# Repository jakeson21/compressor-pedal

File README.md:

# compressor-pedal
This schematic implements [this compressor simulation](https://github.com/jakeson21/circuitjs_designs/blob/main/Compressor-20230116-2301.circuitjs.txt).

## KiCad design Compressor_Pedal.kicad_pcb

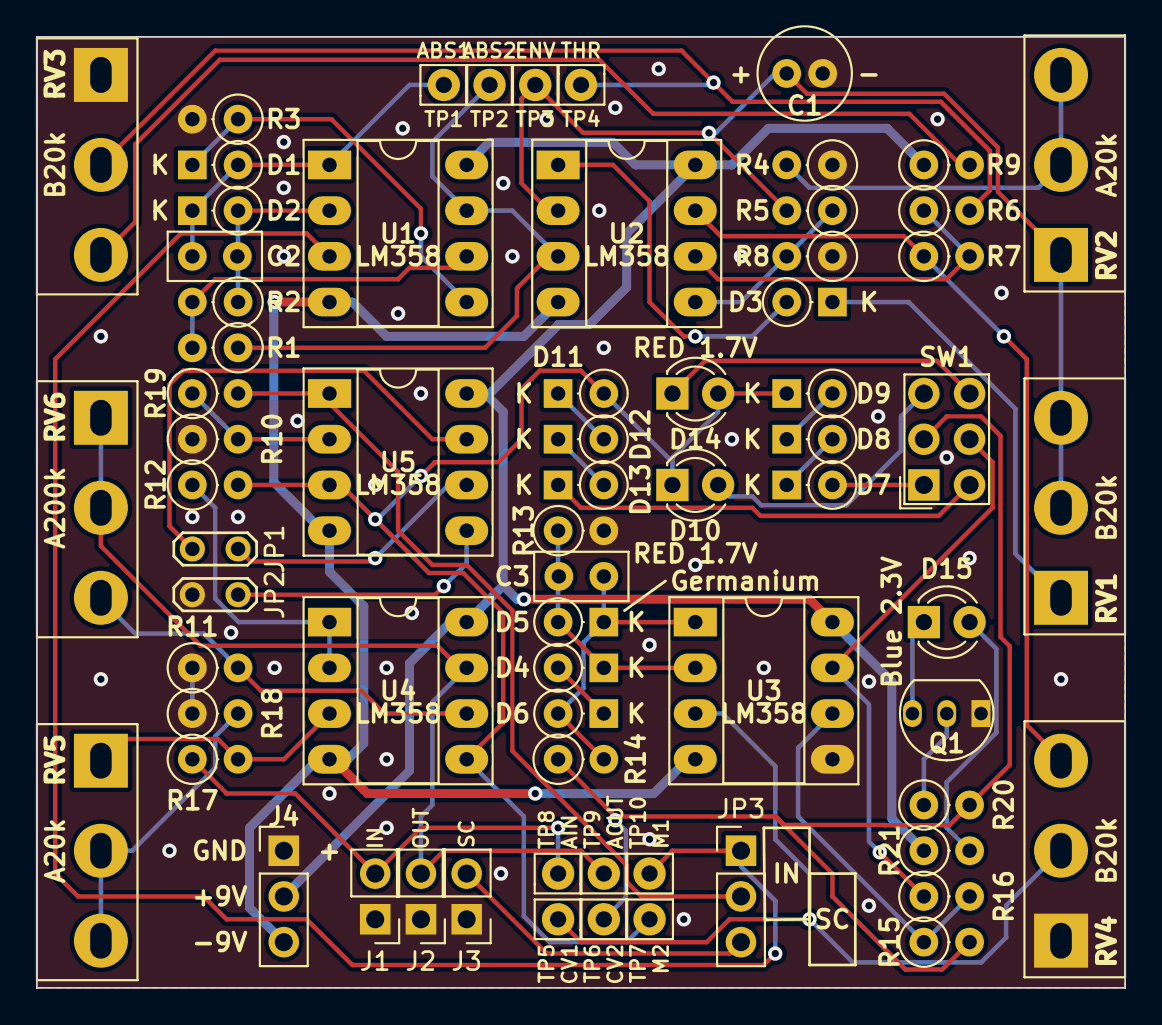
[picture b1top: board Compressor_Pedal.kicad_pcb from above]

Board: 2 copper layers, 60.5 x 52.8 mm, 69 parts (0 on the bottom side), 49 nets.

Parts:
C1: 1uF; C_Radial_D5.0mm_H11.0mm_P2.00mm
C2: 100pF; C_Disc_D5.0mm_W2.5mm_P2.50mm
C3: 1nF; C_Disc_D5.0mm_W2.5mm_P2.50mm
D1, D2, D3, D4, D6, D7, D8, D9, D11, D12, D13: 1N4148; D_DO-35_SOD27_P2.54mm_Vertical_KathodeUp
D5: 1N34A; D_DO-35_SOD27_P2.54mm_Vertical_KathodeUp
D10, D14: RED 1.7V; LED_D3.0mm_FlatTop
D15: Blue 2.3V; LED_D3.0mm_Clear
J1: IN; PinHeader_1x02_P2.54mm_Vertical
J2: OUT; PinHeader_1x02_P2.54mm_Vertical
J3: SC; PinHeader_1x02_P2.54mm_Vertical
J4: Conn_01x03; PinHeader_1x03_P2.54mm_Vertical
JP1, JP2: Jumper_2_Bridged; TestPoint_2Pads_Pitch2.54mm_Drill0.8mm
JP3: Select; PinHeader_1x03_P2.54mm_Vertical
Q1: PN2222A; TO-92_Inline_wide
R1, R2, R3, R11, R18, R20, R21: 10k; R_Axial_DIN0207_L6.3mm_D2.5mm_P2.54mm_Vertical
R4, R10: 4.7k; R_Axial_DIN0207_L6.3mm_D2.5mm_P2.54mm_Vertical
R5, R6, R7, R8, R12, R17, R19: 100k; R_Axial_DIN0207_L6.3mm_D2.5mm_P2.54mm_Vertical
R9: 33k; R_Axial_DIN0207_L6.3mm_D2.5mm_P2.54mm_Vertical
R13: 220k; R_Axial_DIN0207_L6.3mm_D2.5mm_P2.54mm_Vertical
R14: 1k; R_Axial_DIN0207_L6.3mm_D2.5mm_P2.54mm_Vertical
R15, R16: 47k; R_Axial_DIN0207_L6.3mm_D2.5mm_P2.54mm_Vertical
RV1, RV3, RV4: B20k; Potentiometer_Alps_RK163_Single_Horizontal_Pads_Only
RV2, RV5: A20k; Potentiometer_Alps_RK163_Single_Horizontal_Pads_Only
RV6: A200k; Potentiometer_Alps_RK163_Single_Horizontal_Pads_Only
SW1: SW_DPDT_x2; SW_NKK_GW12LJP
TP1: ABS1; Pin_D0.9mm_L10.0mm_W2.4mm_FlatFork
TP2: ABS2; Pin_D0.9mm_L10.0mm_W2.4mm_FlatFork
TP3: ENV; Pin_D0.9mm_L10.0mm_W2.4mm_FlatFork
TP4: THR; Pin_D0.9mm_L10.0mm_W2.4mm_FlatFork
TP5: CV1; Pin_D0.9mm_L10.0mm_W2.4mm_FlatFork
TP6: CV2; Pin_D0.9mm_L10.0mm_W2.4mm_FlatFork
TP7: M2; Pin_D0.9mm_L10.0mm_W2.4mm_FlatFork
TP8: AIN; Pin_D0.9mm_L10.0mm_W2.4mm_FlatFork
TP9: AOUT; Pin_D0.9mm_L10.0mm_W2.4mm_FlatFork
TP10: M1; Pin_D0.9mm_L10.0mm_W2.4mm_FlatFork
U1, U2, U3, U4, U5: LM358; DIP-8_W7.62mm_Socket_LongPads

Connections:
+9V: J4.2, R9.1, R21.1, U1.8 (V+), U2.8 (V+), U3.8 (V+), U4.8 (V+), U5.8 (V+)
-9V: J4.3, U1.4 (V-), U2.4 (V-), U3.4 (V-), U4.4 (V-), U5.4 (V-)
/Volume Control/ctrl_voltage: R7.1, RV4.3, U2.7
/Volume Control/vol_mod: D9.1 (K), D10.1 (K), D11.2 (A), D14.2 (A), R12.2, TP7.1, U4.5 (+), U5.3 (+)
/Volume Detector/signal_in: JP3.1 (A), TP10.1, U1.3 (+)
/input: J1.2 (T), R17.1, TP8.1
/output: J2.2 (T), RV6.1, RV6.2, TP9.1, U4.7
GNDA: C1.2, J1.1 (S), J2.1 (S), J3.1 (S), J4.1, JP2.1 (A), Q1.1 (E), R3.2, R4.1, R8.1, R10.1, R11.1, R13.2, R18.1, RV3.1, RV4.1, U3.5 (+)
unnamed: C2.2, D1.2 (A), D2.1 (K), TP1.1, U1.1
unnamed: D1.1 (K), R3.1, U1.5 (+)
unnamed: C2.1, D2.2 (A), R2.1, U1.2 (-)
unnamed: D3.2 (A), U2.1
unnamed: D3.1 (K), RV1.1
unnamed: D4.2 (A), D6.1 (K)
unnamed: C3.1, D4.1 (K), D5.2 (A), R13.1, U3.2 (-)
unnamed: C3.2, D5.1 (K), D6.2 (A), R14.2, U3.1
unnamed: D7.2 (A), SW1.1 (A)
unnamed: D7.1 (K), D8.2 (A)
unnamed: D8.1 (K), D9.2 (A)
unnamed: D10.2 (A), SW1.3 (C)
unnamed: D11.1 (K), D12.2 (A)
unnamed: D12.1 (K), D13.2 (A)
unnamed: D13.1 (K), SW1.4 (A)
unnamed: D14.1 (K), SW1.6 (C)
unnamed: D15.2 (A), R21.2
unnamed: D15.1 (K), Q1.3 (C)
unnamed: J3.2 (T), JP3.3 (B)
unnamed: JP1.1 (A), U5.6 (-)
unnamed: JP1.2 (B), U5.7
unnamed: JP2.2 (B), U5.5 (+)
unnamed: JP3.2 (C), R19.2, U5.1
unnamed: Q1.2 (B), R20.1
unnamed: R4.2, RV2.2, RV2.3
unnamed: R6.2, RV3.2, TP4.1
unnamed: R9.2, RV3.3
unnamed: R18.2, RV5.2, RV5.3
unnamed: R14.1, R15.2, R20.2, SW1.2 (B), TP6.1
unnamed: R16.1, SW1.5 (B), U3.7
unnamed: R1.2, R2.2, U1.6 (-)
unnamed: R1.1, TP2.1, U1.7, U2.3 (+)
unnamed: C1.1, R5.2, RV1.2, RV1.3, RV2.1, TP3.1, U2.2 (-)
unnamed: R5.1, R8.2, U2.5 (+)
unnamed: R6.1, R7.2, U2.6 (-)
unnamed: RV4.2, TP5.1, U3.3 (+)
unnamed: R15.1, R16.2, U3.6 (-)
unnamed: R17.2, RV5.1, U4.3 (+)
unnamed: R12.1, U4.1, U4.2 (-)
unnamed: R11.2, RV6.3, U4.6 (-)
unnamed: R10.2, R19.1, U5.2 (-)

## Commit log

2023-05-22 adding links
2023-05-26 schematic finished, begin layout
2023-05-30 sent for build
2023-06-14 updates first build to add missing external mod switch - moving to v0.2
2024-02-08 fix problem with external input
